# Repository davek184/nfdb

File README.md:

# USB-C Daughterboard for Norbaforce 

For all models of the Norbaforce (also works with the Norbauer Data Pad). 

Features USB-C port, ESD protection, over voltage protection, CC1 & CC2 resistors to work with USB-C to C cables.  

Finishes on Norbaforces vary greatly.  They were designed for USB mini cables so it is possible a USB-C cable end may not fit depending a finish. In those cases a very light filing of the USB opening using a hobby file can enlarge the opening just enough for the cable.

_(Note there is one PCB that can have a connector for Realforce 1 OR Realforce 2 models)_

# Version No Keyboard Connector

<br><br><br>

# Version Realforce R1 
  
* **Models:** 86U, 87U, 88U, 91U
* **PCB Connector:** LCSC: C265068
* **Cable:** EH to EH (2.5mm pitch), 4 pin, SAME direction, Length 6cm (shielding cable 13cm)

<br><br><br>

# Version Realforce R2 
  
* **Models:** R2 TKL, R2 RGB TKL, RT1 (numpad)
* **PCB Connector:** LCSC: C69152
* **Cable:** PH to PH (2.0mm pitch), 5 pin, REVERSED Direction, Length 11cm

<br><br>

# Manufacturing
<details>
  <summary>Details</summary>
* Manufacturing files are set up for JLCPCB. 
* Thickness does not matter suggest standard 1.6mm 
* "Remove Order Number" option choose "Specify Location" (uses "JLCJLC" on silkscreen for order # position)
* Assemble top side
* Choose assembly file version (No connector: need to solder then yourself, RF1 or RF2 as indicated above in renders)
* Manual part adjustments from KiCad Outputs (already handled in manufacturing files)

| Part              | Adjustment   |
| ----------------- | ------------- |
| USB-C Connector   | Down 5.06mm   |
| JST EH Connector  | Up 3.75mm   |
| JST PH  Connector | Rotate 90°, Down 4mm |

## BOM

| LCSC part # | Description      | Value | Package  | Amount |
| ----------- | ---------------- | ----- | -------- | ------ |
| C261942     | Fuse             |       | 0805     | 1      |
| C7519       | ESD              |       | SOT23-6  | 1      |
| C212411     | Resistor         | 5.1K  | 0805     | 2      |
| C597300     | Capacitor        | 4.7nF | 0805     | 1      |
| C165948     | Connector (USB)  |       | TH       | 1      |
| C265068     | Connector (EH)   | 4 pin | TH       | 1      |
| C69152      | Connector (PH)   | 5 pin | TH       | 1      |

_Note if the capacitor or resistors are out of stock they can be replaced with 0805 sized component with similar specs._
</details>

# EH -> PH Cable Experiments
<details>
  <summary>Details</summary>
Tested a sample cable using manufactured PH crimped wires in an EH cable housing end (LCSC: C161661) to make a PH to EH cable without manually crimping.  Worked without issues after 350 connection cycles.  Potential could use R2 daughterboard connector can be used for both R2 and R1 boards.

</details>

# Notes
<details>
  <summary>R2 NFDB and the Realforce RT1 (Topre numpad)</summary>

The R2 NFDB is compatible with the Topre Realforce RT1 numpad (released in 2024), which shares a similar footprint to the predecessor Realforce 23u.  

</details>  
<details>
  <summary>Photos</summary>

Norbaforce MKI (cutout is USB shape no issues with fit)

Norbaforce MKIII (unfinished no fit issues)

Norbaforce MKII RF2

Norbaforce MKII (slight internal filing was needed)

Norbauer Data Pad and the R1 NFDB

Norbauer Data Pad with RT1 pcb - use R2 NFDB

</details>

# Special thanks 
* Nekotato: for requesting, testing & driving this project
* Techbeezin: for test fitting the vast collection of Norbaforces 
* Cipulot: answering various questions regarding Realforce and general electrical questions/advice
* d0nk: for pre-testing the R2 OEM cabling/pinout on RT1

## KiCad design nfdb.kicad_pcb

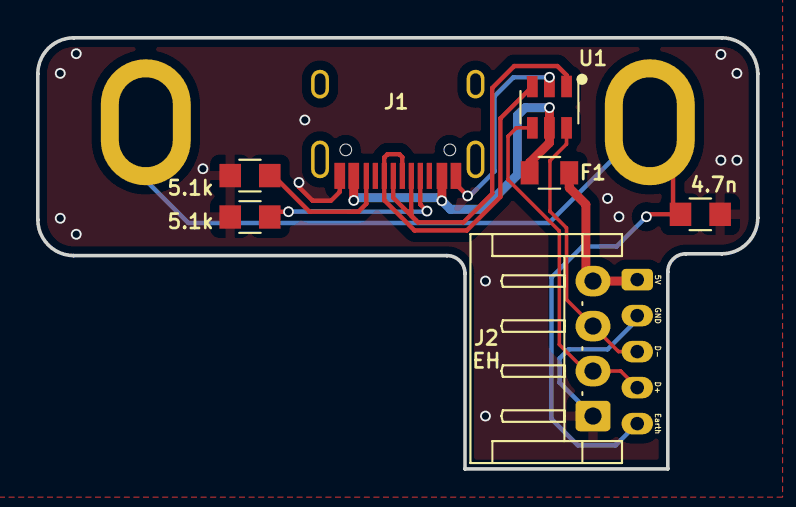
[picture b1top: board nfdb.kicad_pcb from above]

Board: 2 copper layers, 40.0 x 24.0 mm, 8 parts (0 on the bottom side), 9 nets.

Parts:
C1: 4.7n; R_0805
F1: Polyfuse_Small; F_0805
J1: TYPE-C-31-M-12; HRO-TYPE-C-31-M-12
J2: JST_EH_S4B-EH_1x04_P2.50mm_Horizontal
J3: JST_PH_S5B-PH-K_1x05_P2.00mm_Horizontal
R1, R2: 5.1k; R_0805
U1: USBLC6-2SC6

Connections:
D+: J2.2, J3.4, U1.4 (I/O2)
D-: J2.3, J3.3, U1.6 (I/O1)
Earth: C1.2, J3.5
GND: C1.1, J1.1 (GND), J1.12 (GND), J2.1, J3.2, R1.2, R2.2, U1.2 (GND)
unnamed: J1.4 (CC1), R1.1
unnamed: J1.5 (DN2), J1.7 (DN1), U1.1 (I/O1)
unnamed: J1.6 (DP1), J1.8 (DP2), U1.3 (I/O2)
unnamed: J1.10 (CC2), R2.1
VBUS: F1.1, F1.2, J1.2 (VBUS), J1.11 (VBUS), J2.4, J3.1, U1.5 (VBUS)

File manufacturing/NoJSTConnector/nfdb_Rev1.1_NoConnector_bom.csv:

Designator,Footprint,Quantity,Value,LCSC Part #
C1,R_0805,1,4.7n, C597300
F1,F_0805,1,Polyfuse_Small, C261942
J1,HRO-TYPE-C-31-M-12,1,TYPE-C-31-M-12, C165948
"R1, R2",R_0805,2,5.1k, C212411
U1,USBLC6-2SC6,1,USBLC6-2SC6, C7519

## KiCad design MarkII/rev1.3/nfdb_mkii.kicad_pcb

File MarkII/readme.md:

# USB C Daughter/Breakout board for Norbaforce 

For the Norbaforce (MKii/iii). Features USB-C port, ESD protection, over voltage protection, CC1 & CC2 resistors to work with USB-C to C cables.  

_(2 daughterboards in this design, RF1 & RF2, to save money manufacturing)_

[TODO: Once samples arrive include photo with riser)

## Realforce R1 
**Models:** 86U, 87U, 88U, 91U

**Cable:** EH to EH (2.5mm pitch), 4 pin, SAME direction, Length 6cm (shielding cable 13cm)

## Realforce R2 
**Models:** R2 TKL, R2 RGB TKL

**Cable:** PH to PH (2.0mm pitch), 5 pin, REVERSED Direction, Length 11cm

## Production
* Production files are set up for JLCPCB.  
* "Remove Order Number" option choose "Specify Location" (uses "JLCJLC" on silkscreen for order # position)
* _Note only Gerber file is included so part files would need to be generated from KiCad.  In addition these would need to be manually soldered for the USB riser with pin headers_

| Part              | Adjustment   |
| ----------------- | ------------- |
| USB-C Connector   | Down 5.06mm   |
| JST EH Connector  | Up 3.75mm   |
| JST PH  Connector | Rotate 90°, Right ~0.3mm |

## BOM

| LCSC part # | Description   | Value | Package  | Amount |
| ----------- | ------------- | ----- | -------- | ------:|
| C261942     | Fuse          |       | 0805     | 2      |
| C7519       | ESD           |       | SOT23-6  | 2      |
| C212411     | Resistor      | 5.1K  | 0805     | 4      |
| C21217      | Capacitor     | 4.7nF | 0805     | 2      |
| C165948     | Connector     |       | TH       | 2      |
| C265068     | Connector (EH)| 4 pin | TH       | 2      |
| C265104     | Connector (PH)| 5 pin | SMT      | 2      |
(Pin headers 2.54mm pitch)

_Note if the capacitor or resistors are out of stock they can be replaced with 0805 sized component with similar specs._

## Revisions
1.0
* Initial prototype

1.1
* Added usb riser section to better fit Norbaforce
* Updated Design so that both RF1 & RF2 models can be printed in one file (saves money when manufacturing)
* Flipped silkscreen orientation for those with a clear case.  
* Updated JST PH connector to surface mount instead of through hole.

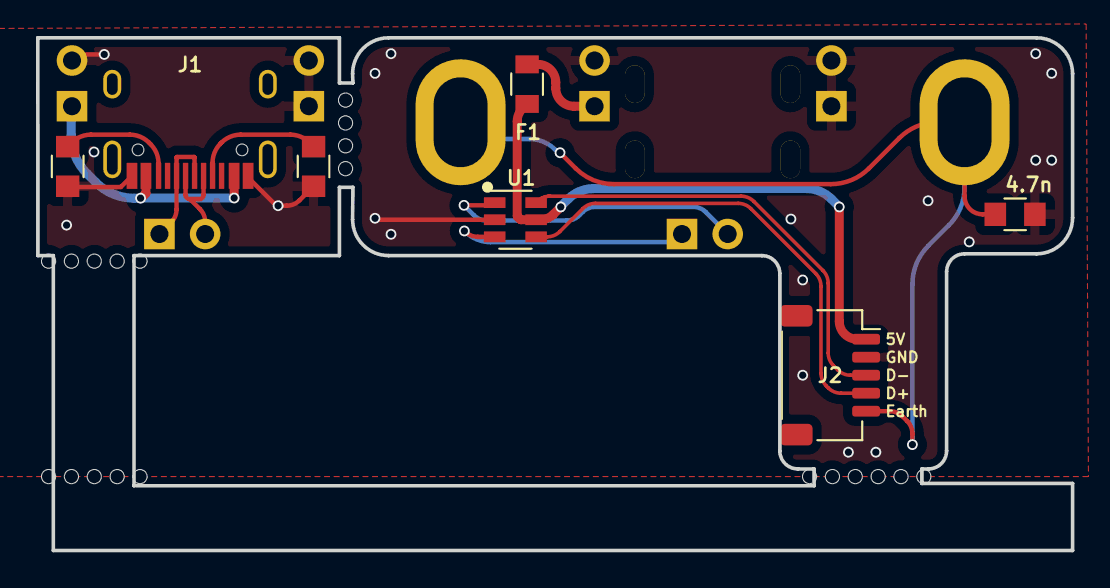
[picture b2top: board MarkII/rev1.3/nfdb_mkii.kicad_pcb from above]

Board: 2 copper layers, 57.5 x 28.5 mm, 16 parts (1 on the bottom side), 9 nets.

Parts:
C1: 4.7n; R_0805
F1: Polyfuse_Small; F_0805
G1: LOGO; MegaMan7
J1, J6: TYPE-C-31-M-12; HRO-TYPE-C-31-M-12
J2: JST_SH_SM05B-SRSS-TB_1x05-1MP_P1.00mm_Horizontal
PH1, PH2, PH3, PH4, PH5, PH6: PinHeader_1x02_P2.54mm_Vertical
R1, R2: 5.1k; R_0805
REFr: mb; breakaway-mousebites
U1: USBLC6-2SC6

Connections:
D+: J2.4, U1.4 (I/O2)
D-: J2.3, U1.6 (I/O1)
Earth: C1.2, J2.5
GND: C1.1, J1.1 (GND), J1.12 (GND), J2.2, PH1.2, PH2.1, PH2.2, PH4.2, PH5.1, PH5.2, R1.2, R2.2, U1.2 (GND)
unnamed: J1.4 (CC1), R2.1
unnamed: J1.5 (DN2), J1.7 (DN1), PH3.2, PH6.2, U1.1 (I/O1)
unnamed: J1.6 (DP1), J1.8 (DP2), PH3.1, PH6.1, U1.3 (I/O2)
unnamed: J1.10 (CC2), R1.1
VBUS: F1.1, F1.2, J1.2 (VBUS), J1.11 (VBUS), J2.1, PH1.1, PH4.1, U1.5 (VBUS)

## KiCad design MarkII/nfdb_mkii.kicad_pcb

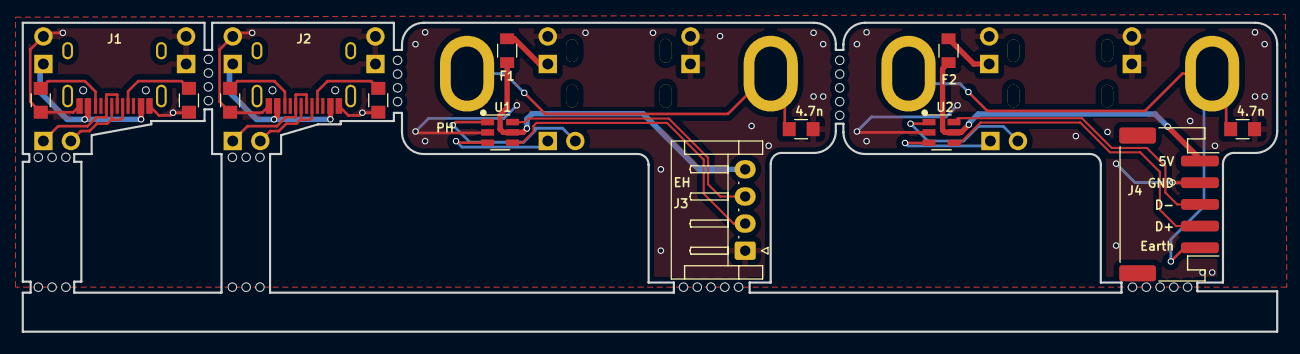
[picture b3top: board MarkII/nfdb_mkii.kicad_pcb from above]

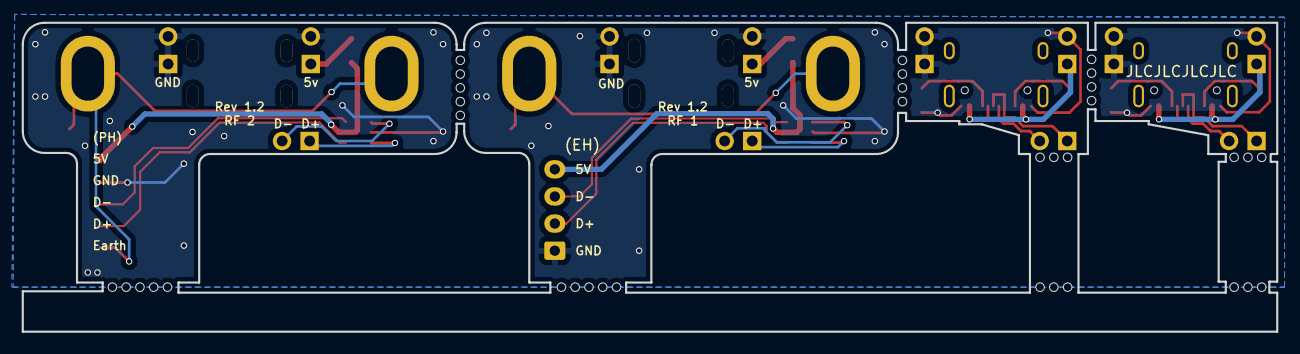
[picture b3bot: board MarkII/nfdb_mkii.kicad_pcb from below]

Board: 2 copper layers, 115.7 x 28.5 mm, 30 parts (2 on the bottom side), 9 nets.

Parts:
C1, C2: 4.7n; R_0805
F1, F2: Polyfuse_Small; F_0805
G1, G1#2: LOGO; MegaMan7
J1, J2, J5, J6: TYPE-C-31-M-12; HRO-TYPE-C-31-M-12
J3: JST_EH_S4B-EH_1x04_P2.50mm_Horizontal
J4: JST_PH_S5B-PH-SM4-TB_1x05-1MP_P2.00mm_Horizontal
PH1, PH2, PH3, PH4, PH5, PH6, PH7, PH8, PH9, PH10, PH11, PH12: PinHeader_1x02_P2.54mm_Vertical
R1, R1#2, R2, R2#2: 5.1k; R_0805
U1, U2: USBLC6-2SC6

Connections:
D+: J3.2, J4.4, U1.4 (I/O2), U2.4 (I/O2)
D-: J3.3, J4.3, U1.6 (I/O1), U2.6 (I/O1)
Earth: C1.2, C2.2, J4.5
GND: C1.1, C2.1, J1.1 (GND), J1.12 (GND), J2.1 (GND), J2.12 (GND), J3.1, J4.2, PH1.2, PH3.1, PH3.2, PH4.2, PH6.1, PH6.2, PH7.2, PH9.1, PH9.2, PH10.2, PH12.1, PH12.2, R1.2, R1#2.2, R2.2, R2#2.2, U1.2 (GND), U2.2 (GND)
unnamed: J1.4 (CC1), J2.4 (CC1), R2.1, R2#2.1
unnamed: J1.5 (DN2), J1.7 (DN1), J2.5 (DN2), J2.7 (DN1), PH2.2, PH5.2, PH8.2, PH11.2, U1.1 (I/O1), U2.1 (I/O1)
unnamed: J1.6 (DP1), J1.8 (DP2), J2.6 (DP1), J2.8 (DP2), PH2.1, PH5.1, PH8.1, PH11.1, U1.3 (I/O2), U2.3 (I/O2)
unnamed: J1.10 (CC2), J2.10 (CC2), R1.1, R1#2.1
VBUS: F1.1, F1.2, F2.1, F2.2, J1.2 (VBUS), J1.11 (VBUS), J2.2 (VBUS), J2.11 (VBUS), J3.4, J4.1, PH1.1, PH4.1, PH7.1, PH10.1, U1.5 (VBUS), U2.5 (VBUS)

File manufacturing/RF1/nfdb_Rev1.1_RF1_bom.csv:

Designator,Footprint,Quantity,Value,LCSC Part #
C1,R_0805,1,4.7n, C597300
F1,F_0805,1,Polyfuse_Small, C261942
J1,HRO-TYPE-C-31-M-12,1,TYPE-C-31-M-12, C165948
J2,JST_EH_S4B-EH_1x04_P2.50mm_Horizontal,1,JST_EH_S4B-EH_1x04_P2.50mm_Horizontal, C265068
"R1, R2",R_0805,2,5.1k, C212411
U1,USBLC6-2SC6,1,USBLC6-2SC6, C7519

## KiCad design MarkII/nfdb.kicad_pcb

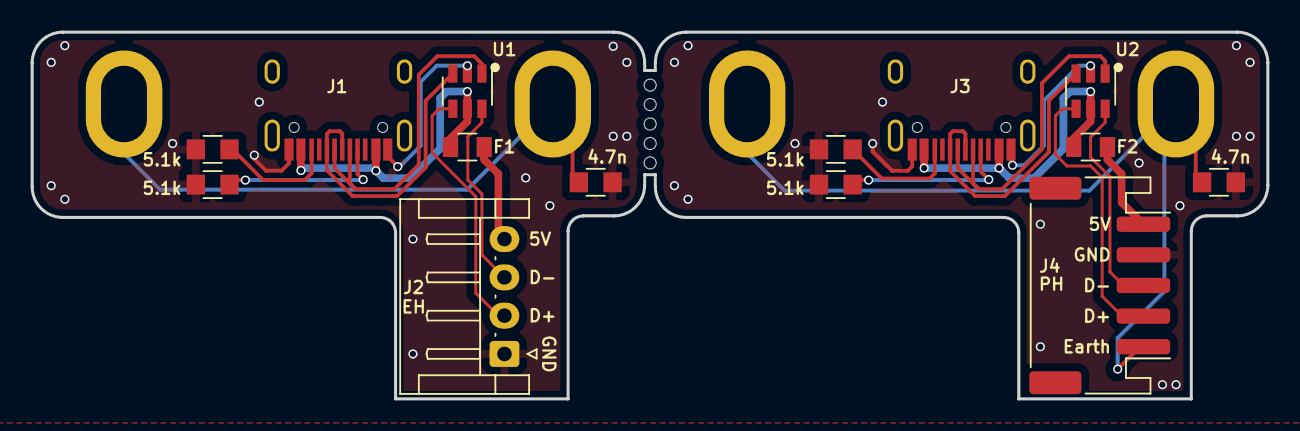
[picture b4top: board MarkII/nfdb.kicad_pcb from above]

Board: 2 copper layers, 80.7 x 24.0 mm, 14 parts (0 on the bottom side), 9 nets.

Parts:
C1, C2: 4.7n; R_0805
F1, F2: Polyfuse_Small; F_0805
J1, J3: TYPE-C-31-M-12; HRO-TYPE-C-31-M-12
J2: JST_EH_S4B-EH_1x04_P2.50mm_Horizontal
J4: JST_PH_S5B-PH-SM4-TB_1x05-1MP_P2.00mm_Horizontal
R1, R2, R3, R4: 5.1k; R_0805
U1, U2: USBLC6-2SC6

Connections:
D+: J2.2, J4.4, U1.4 (I/O2), U2.4 (I/O2)
D-: J2.3, J4.3, U1.6 (I/O1), U2.6 (I/O1)
Earth: C1.2, C2.2, J4.5
GND: C1.1, C2.1, J1.1 (GND), J1.12 (GND), J2.1, J3.1 (GND), J3.12 (GND), J4.2, R1.2, R2.2, R3.2, R4.2, U1.2 (GND), U2.2 (GND)
unnamed: J1.4 (CC1), J3.4 (CC1), R1.1, R4.1
unnamed: J1.5 (DN2), J1.7 (DN1), J3.5 (DN2), J3.7 (DN1), U1.1 (I/O1), U2.1 (I/O1)
unnamed: J1.6 (DP1), J1.8 (DP2), J3.6 (DP1), J3.8 (DP2), U1.3 (I/O2), U2.3 (I/O2)
unnamed: J1.10 (CC2), J3.10 (CC2), R2.1, R3.1
VBUS: F1.1, F1.2, F2.1, F2.2, J1.2 (VBUS), J1.11 (VBUS), J2.4, J3.2 (VBUS), J3.11 (VBUS), J4.1, U1.5 (VBUS), U2.5 (VBUS)

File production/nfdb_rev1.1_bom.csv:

Designator,Footprint,Quantity,Value,LCSC Part #
"C1, C2",R_0805,2,4.7n,C21217
"F1, F2",F_0805,2,Polyfuse_Small,C261942
"J1, J3",HRO-TYPE-C-31-M-12,2,TYPE-C-31-M-12,C165948
J2,JST_EH_S4B-EH_1x04_P2.50mm_Horizontal,1,JST_EH_S4B-EH_1x04_P2.50mm_Horizontal,C265068
J4,JST_PH_S5B-PH-SM4-TB_1x05-1MP_P2.00mm_Horizontal,1,JST_PH_S5B-PH-SM4-TB_1x05-1MP_P2.00mm_Horizontal,C265104
"R1, R2, R3, R4",R_0805,4,5.1k,C212411
"U1, U2",USBLC6-2SC6,2,USBLC6-2SC6,C7519

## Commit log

2022-12-31 MKi & MKii seperation to different files
2023-01-06 rev 1.1
2023-01-21 Fixed mkii R2 ground traces
2023-01-23 Rev 1.3 unified design (use different cable for RF1 vs RF2
    Rev 1.3 unified design (use different cable for RF1 vs RF2
2023-01-28 Went back to 1 db design to rule them all
2023-01-29 Update README.md
    Added Photos
2023-02-10 Silk Screen Adjustment
2023-02-22 Rev 1.3
    Small Silkscreen adjustment
